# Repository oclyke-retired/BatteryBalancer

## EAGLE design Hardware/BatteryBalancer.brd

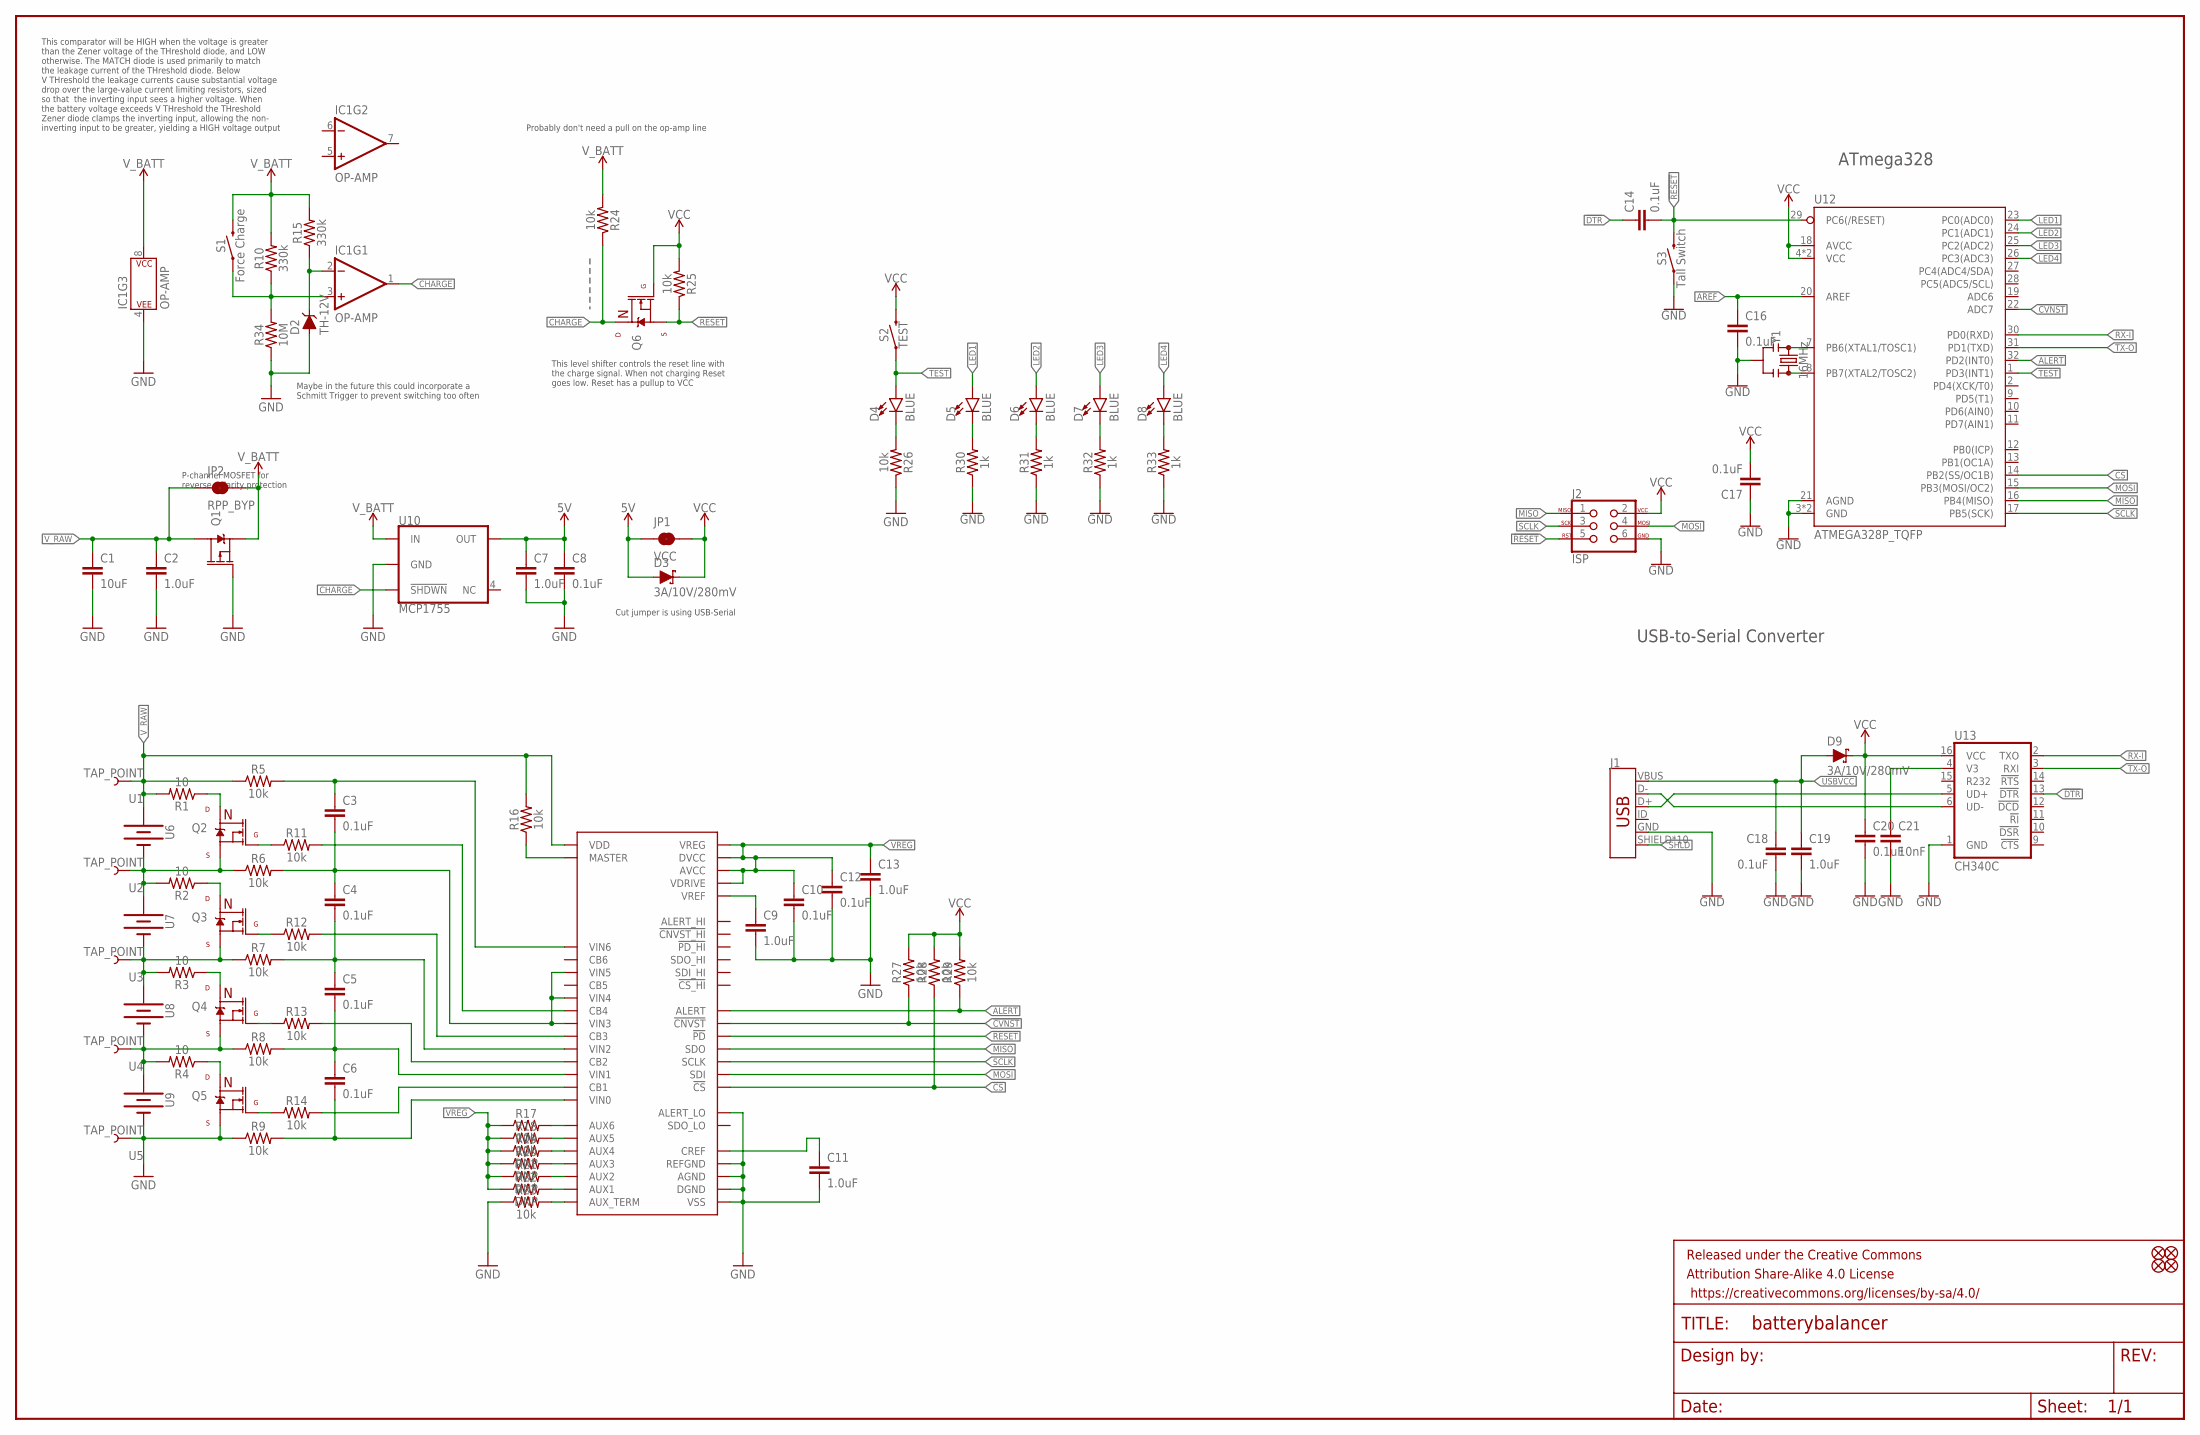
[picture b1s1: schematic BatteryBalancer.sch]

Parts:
C1: 10uF; 1210
C2: 1.0uF; 1206
C3, C4, C5, C6, C8, C10, C12, C14, C16, C17, C18, C20: 0.1uF; 0603
C7, C9, C11, C13, C19: 1.0uF; 0603
C21: 10nF; 0603
D2: TH-12V; SOT23-3
D3, D9: 3A/10V/280mV; SOD-323
D4, D5, D6, D7, D8: BLUE; LED-0603
FD1, FD2, FD3, FD4: FIDUCIALUFIDUCIAL; FIDUCIAL-MICRO
FRAME1: FRAME-LEDGER; CREATIVE_COMMONS
IC1: OP-AMP; SO08
J1: USB_MICRO-B_HALF_PTH_MILL; USB-MICROB-PTH-MILL
J2: ISP; 2X3_TEST_POINTS
JP1: VCC; SMT-JUMPER_2_NC_TRACE_SILK
JP2: RPP_BYP; SMT-JUMPER_2_NC_TRACE_SILK
Q1: MOSFET_PCH-IRLML2244; SOT23-3
Q2, Q3, Q4, Q5, Q6: AMP_MOSFET_NCH-2N7002K; SOT23-3
R1, R2, R3, R4: 10; 1206
R5, R6, R7, R8, R9, R11, R12, R13, R14, R16, R17, R18, R23, R24, R25, R26, R27, R28, R29: 10k; 0603
R10, R15: 330k; 0603
R19, R20, R21, R22: DNP; AXIAL-0.3
R30, R31, R32, R33: 1k; 0603
R34: 10M; 0603
S1: Force Charge; TACTILE_SWITCH_SMD_5.2MM
S2: TEST; TACTILE_SWITCH_SMD_5.2MM
S3: Tall Switch; TACTILE_SWITCH_SMD_5.2MM
U1, U2, U3, U4, U5: TAP_POINT; 1X01_SMD_0.1IN
U10: MCP1755; SOT23-5
U11: AD7280A; LQFP-48
U12: ATMEGA328P_TQFP; TQFP32-08
U13: CH340C; SO016
Y1: 16MHz; RESONATOR-SMD-3.2X1.3

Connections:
5V: C7.1, C8.1, D3.A, JP1.1, U10.5 (OUT)
!CS: R28.1, U11.21 (!CS), U12.14 (PB2(SS/OC1B))
!CVNST: R27.1, U11.24 (!CNVST), U12.22 (ADC7)
!DTR: C14.1, U13.13 (!DTR)
!RESET: C14.2, J2.5, Q6.2 (S), R25.1, S3.3 (2), S3.4 (2), U11.15 (!PD), U12.29 (PC6(/RESET))
ALERT: R29.1, U11.27 (ALERT), U12.32 (PD2(INT0))
AREF: C16.1, U12.20 (AREF)
CHARGE: IC1.1 (OUT), Q6.3 (D), R24.1, U10.3 (!SHDWN)
D+: J1.D+, U13.5 (UD+)
D-: J1.D-, U13.6 (UD-)
GND: C1.2, C2.2, C7.2, C8.2, C9.2, C10.2, C11.2, C12.2, C13.2, C16.2, C17.1, C18.2, C19.2, C20.2, C21.2, D2.1 (A), IC1.4 (P$V-), J1.GND, J2.6, Q1.1 (G), Q5.2 (S), R9.1, R23.1, R26.1, R30.1, R31.1, R32.1, R33.1, R34.1, S3.1, S3.2 (1), U5.1, U10.2 (GND), U11.17 (VSS), U11.20 (DGND), U11.28 (ALERT_LO), U11.31 (AGND), U11.41 (REFGND), U12.3 (GND), U12.5 (GND), U12.21 (AGND), U13.1 (GND), Y1.2
LED1: D5.A, U12.23 (PC0(ADC0))
LED2: D6.A, U12.24 (PC1(ADC1))
LED3: D7.A, U12.25 (PC2(ADC2))
LED4: D8.A, U12.26 (PC3(ADC3))
MISO: J2.1, U11.26 (SDO), U12.16 (PB4(MISO))
MOSI: J2.4, U11.23 (SDI), U12.15 (PB3(MOSI/OC2))
unnamed: U12.7 (PB6(XTAL1/TOSC1)), Y1.1
unnamed: U12.8 (PB7(XTAL2/TOSC2)), Y1.3
unnamed: Q2.3 (D), R1.1
unnamed: Q2.2 (S), R2.2, R6.1, U2.1
unnamed: Q3.3 (D), R2.1
unnamed: Q3.2 (S), R3.2, R7.1, U3.1
unnamed: Q4.3 (D), R3.1
unnamed: Q4.2 (S), R4.2, R8.1, U4.1
unnamed: Q5.3 (D), R4.1
unnamed: Q2.1 (G), R11.1
unnamed: Q3.1 (G), R12.1
unnamed: R16.1, U11.14 (MASTER)
unnamed: Q4.1 (G), R13.1
unnamed: Q5.1 (G), R14.1
unnamed: C6.2, R9.2, U11.13 (VIN0)
unnamed: R14.2, U11.12 (CB1)
unnamed: C5.2, C6.1, R8.2, U11.11 (VIN1)
unnamed: R13.2, U11.10 (CB2)
unnamed: C4.2, C5.1, R7.2, U11.9 (VIN2)
unnamed: R12.2, U11.8 (CB3)
unnamed: R22.P$2 (2), U11.38 (AUX1)
unnamed: R11.2, U11.6 (CB4)
unnamed: C3.1, R5.2, U11.1 (VIN6)
unnamed: C3.2, C4.1, R6.2, U11.3 (VIN5), U11.5 (VIN4), U11.7 (VIN3)
unnamed: C9.1, U11.40 (VREF)
unnamed: R17.2, U11.33 (AUX6)
unnamed: C11.1, U11.39 (CREF)
unnamed: R23.2, U11.32 (AUX_TERM)
unnamed: R18.2, U11.34 (AUX5)
unnamed: R21.P$2 (2), U11.37 (AUX2)
unnamed: R20.P$2 (2), U11.36 (AUX3)
unnamed: R19.P$2 (2), U11.35 (AUX4)
unnamed: D4.C, R26.2
unnamed: C21.1, U13.4 (V3)
unnamed: D8.C, R33.2
unnamed: IC1.3 (+IN), R10.1, R34.2, S1.1, S1.2 (1)
unnamed: D2.3 (C), IC1.2 (-IN), R15.1
unnamed: D7.C, R32.2
unnamed: D6.C, R31.2
unnamed: D5.C, R30.2
RX-I: U12.30 (PD0(RXD)), U13.2 (TXO)
SCLK: J2.3, U11.22 (SCLK), U12.17 (PB5(SCK))
SHLD: J1.SHIELD, J1.SHIELD2 (SHIELD), J1.SHIELD3 (SHIELD), J1.SHIELD4 (SHIELD), J1.SHIELD5 (SHIELD), J1.SHIELD6 (SHIELD), J1.SHIELD7 (SHIELD), J1.SHIELD8 (SHIELD), J1.SHIELD9 (SHIELD), J1.SHIELD10 (SHIELD)
TEST: D4.A, S2.1, S2.2 (1), U12.1 (PD3(INT1))
TX-O: U12.31 (PD1(TXD)), U13.3 (RXI)
USBVCC: C18.1, C19.1, D9.A, J1.VBUS
VCC: C17.2, C20.1, D3.C, D9.C, J2.2, JP1.2, Q6.1 (G), R25.2, R27.2, R28.2, R29.2, S2.3 (2), S2.4 (2), U12.4 (VCC), U12.6 (VCC), U12.18 (AVCC), U13.16 (VCC)
VREG: C10.1, C12.1, C13.1, R17.1, R18.1, R19.P$1 (1), R20.P$1 (1), R21.P$1 (1), R22.P$1 (1), U11.18 (VREG), U11.19 (DVCC), U11.29 (VDRIVE), U11.30 (AVCC)
V_BATT: IC1.8 (P$V+), JP2.2, Q1.2 (S), R10.2, R15.2, R24.2, S1.3 (2), S1.4 (2), U10.1 (IN)
V_RAW: C1.1, C2.1, JP2.1, Q1.3 (D), R1.2, R5.1, R16.2, U1.1, U11.16 (VDD)

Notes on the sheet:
ATmega328
USB-to-Serial Converter
P-channel MOSFET for reverse polarity protection
This comparator will be HIGH when the voltage is greater than the Zener voltage of the THreshold diode, and LOW otherwise. The MATCH diode is used primarily to match the leakage current of the THreshold diode. Below V THreshold the leakage currents cause substantial voltage drop over the large-valu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
Maybe in the future this could incorporate a Schmitt Trigger to prevent switching too often
Cut jumper is using USB-Serial
This level shifter controls the reset line with the charge signal. When not charging Reset goes low. Reset has a pullup to VCC
Probably don't need a pull on the op-amp line

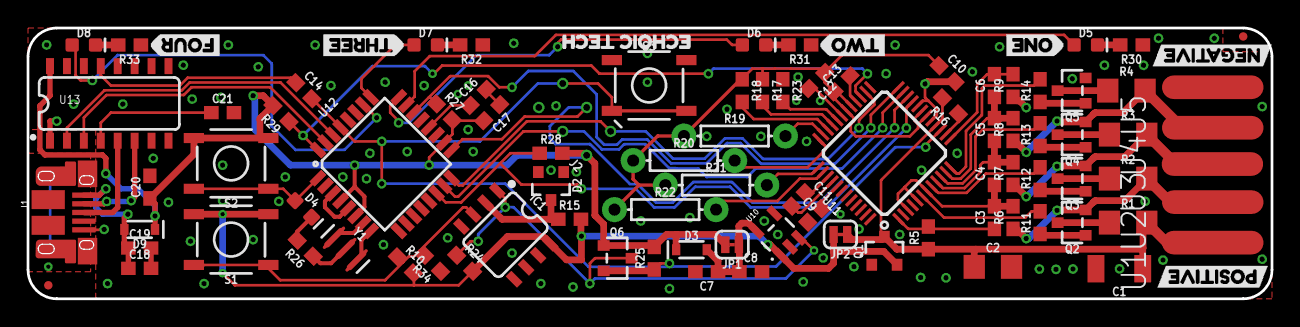
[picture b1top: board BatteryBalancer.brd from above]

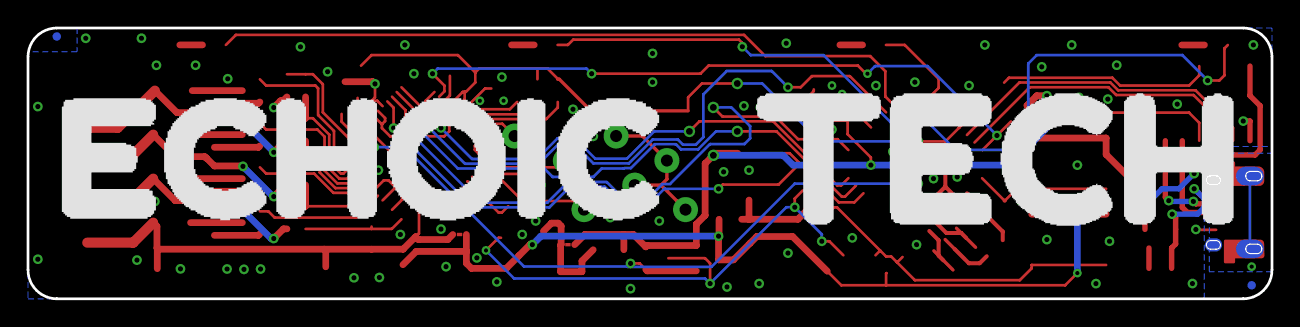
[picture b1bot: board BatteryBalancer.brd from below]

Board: 2 copper layers, 93.3 x 20.3 mm, 100 parts (4 on the bottom side), 67 nets.

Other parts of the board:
U$1: POSITIVE1
U$2: NEGATIVE0
U$3: ONE3
U$4: TWO4
U$5: THREE6
U$6: FOUR5
U$7: ECHOIC_TECH7
U$8: ECHOIC#JPG
U$9: TECH#JPG

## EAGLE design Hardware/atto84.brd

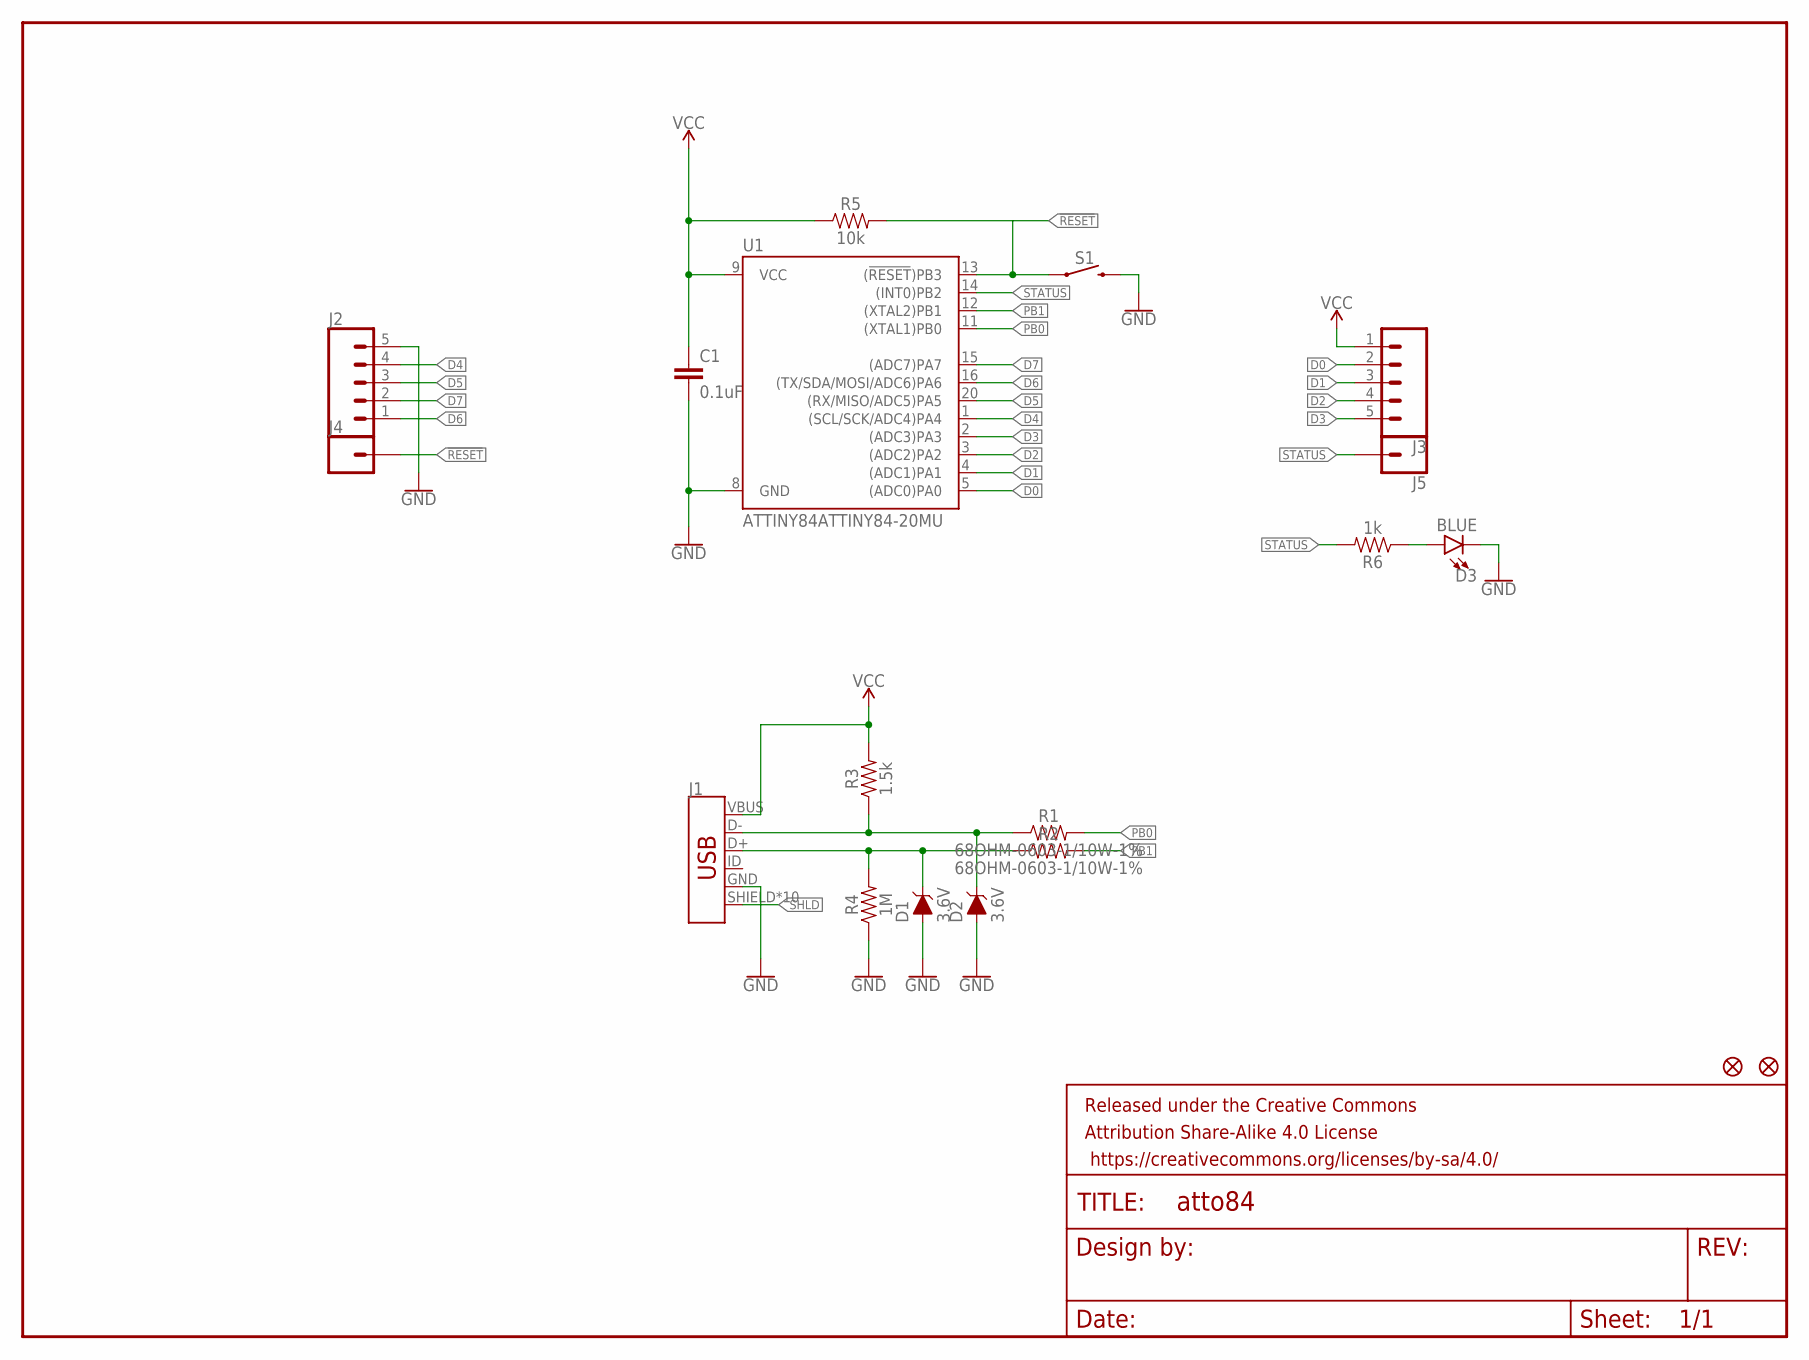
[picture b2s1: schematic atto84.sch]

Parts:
C1: 0.1uF; 0603
D1, D2: 3.6V; SOD-323
D3: BLUE; LED-0603
FD1, FD2: FIDUCIALUFIDUCIAL; FIDUCIAL-MICRO
FRAME1: FRAME-LETTER; CREATIVE_COMMONS
J1: USB_MICRO-B_HALF_PTH_MILL; USB-MICROB-PTH-MILL
J2, J3: CONN_05NO_SILK; 1X05_NO_SILK
J4, J5: CONN_01PTH_NO_SILK_YES_STOP; 1X01_NO_SILK
R1, R2: 68OHM-0603-1/10W-1%; 0603
R3: 1.5k; 0603
R4: 1M; 0603
R5: 10k; 0603
R6: 1k; 0603
S1: MOMENTARY-SWITCH-SPST-SMD-6.0X3.5MM; TACTILE_SWITCH_SMD_6.0X3.5MM
U1: ATTINY84ATTINY84-20MU; QFN20

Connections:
!RESET: J4.1, R5.2, S1.1, U1.13 ((!RESET!)PB3)
D0: J3.2, U1.5 ((ADC0)PA0)
D1: J3.3, U1.4 ((ADC1)PA1)
D2: J3.4, U1.3 ((ADC2)PA2)
D3: J3.5, U1.2 ((ADC3)PA3)
D4: J2.4, U1.1 ((SCL/SCK/ADC4)PA4)
D5: J2.3, U1.20 ((RX/MISO/ADC5)PA5)
D6: J2.1, U1.16 ((TX/SDA/MOSI/ADC6)PA6)
D7: J2.2, U1.15 ((ADC7)PA7)
D+: D1.C, J1.D+, R2.1, R4.2
D-: D2.C, J1.D-, R1.1, R3.1
GND: C1.2, D1.A, D2.A, D3.C, J1.GND, J2.5, R4.1, S1.2, U1.8 (GND)
unnamed: D3.A, R6.1
PB0: R1.2, U1.11 ((XTAL1)PB0)
PB1: R2.2, U1.12 ((XTAL2)PB1)
SHLD: J1.SHIELD, J1.SHIELD2 (SHIELD), J1.SHIELD3 (SHIELD), J1.SHIELD4 (SHIELD), J1.SHIELD5 (SHIELD), J1.SHIELD6 (SHIELD), J1.SHIELD7 (SHIELD), J1.SHIELD8 (SHIELD), J1.SHIELD9 (SHIELD), J1.SHIELD10 (SHIELD)
STATUS: J5.1, R6.2, U1.14 ((INT0)PB2)
VCC: C1.1, J1.VBUS, J3.1, R3.2, R5.1, U1.9 (VCC)

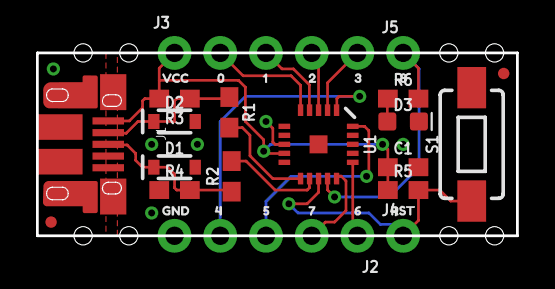
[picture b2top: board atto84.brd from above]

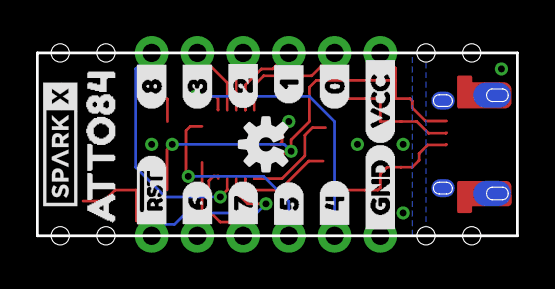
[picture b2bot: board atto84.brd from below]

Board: 2 copper layers, 26.7 x 10.2 mm, 47 parts (15 on the bottom side), 18 nets.

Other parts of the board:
U$1: 00
U$2: 11
U$3: 22
U$4: 33
U$5: 44
U$6: 55
U$7: 66
U$8: 77
U$9: RST8
U$10: VCC10
U$11: GND9
U$12: 81
U$13: ATTO8411
U$14: SPARKX-SMALL
U$15: _#RST0
U$16: _42
U$17: _53
U$18: _64
U$19: _75
U$20: _GND1
U$21: VCC_5
U$22: 0_4
U$23: 1_3
U$24: 2_2
U$25: 3_1
U$26: 8_0
U$27: OSHW-LOGO-S

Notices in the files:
parts and their libraries:
SparkFun-Aesthetics: Licensing: Creative Commons ShareAlike 4.0 International - https://creativecommons.org/licenses/by-sa/4.0
SparkFun-Aesthetics: Released under the Creative Commons Attribution Share-Alike 4.0 License
SparkFun-Aesthetics: https://creativecommons.org/licenses/by-sa/4.0
